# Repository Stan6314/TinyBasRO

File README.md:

Microcomputer TinyBasRO
======================

The TinyBasRO microcomputer is a very simple device that even an electrical engineering beginner should be able to assemble and put into operation. It resembles simple 8-bit computers from the 1980s. After assembly, it can be programmed very easily using the Tiny BASIC language, which should be manageable even for those who have never programmed before. The basis is a small 32-bit RISC-V processor cooperating with serial I2C memory, where the user-created program is stored.

A microcomputer is suitable for the first introduction to computing technology when teaching hardware and software. It can be used not only for educational purposes, but can also be used as a control element for simple electronic devices.

Technical data for TinyBasRO
----------------------------

*   TinyBasHW_KiCad - HW documents (schematic and printed circuit board) in KiCad 9.0 format
*   src - Source files for TinyBasRO for CH32V003 created in ch32fun development environment
*   Bin - Compiled binary content in HEX format for direct loading into CH32V003 memory
*   Manuals - Manuals for HW, Tiny BASIC programming language and its examples and advice for beginners
*   EEPROM_examples - Contents of serial EEPROM memory in HEX format with examples of 8 ready-made Tiny BASIC sample programs for loading into microcomputer memory

Requirements for building and operating a TinyBasRO
---------------------------------------------------

*   Printed circuit board
*   Electrical components according to the list in the TinyBasRO_HW manual
*   WCHLinkE programmer for programming CH32V003
*   OLED display 128x128 with SH1107 driver
*   Keyboard CardKB from M5STACK
*   5V power supply

Using a microcomputer
---------------------

The assembled microcomputer only requires a 5 V power supply, OLED display 128x128 with SH1107 driver and CardKB keyboard. The board has several interfaces for connecting expansion modules via the I2C bus or controlled elements via the input/output connector. In addition, the TinyBasRO allows you to easily light up a string of up to 100 WS2812 LEDs compared to computer TinyBasRV.

After debugging the program, the TinyBasRO microcomputer can work independently without a monitor and keyboard and control, for example, some LED lighting effects.

* * *

Mikropočítač TinyBasRO
======================

Mikropočítač TinyBasRO je velmi jednoduché zařízení, které by měl dokázat sestavit a uvést do provozu i elektrotechnický začátečník. Podobá se jednoduchým 8bitovým počítačům z 80tých let. Po sestavení jej lze velmi jednoduše programovat pomocí jazyka Tiny BASIC, který by měl zvládnout i ten, kdo dříve neprogramoval. Základem je malý 32bitový RISC-V procesor spolupracující se sériovou I2C pamětí, kam se ukládá uživatelem tvořený program.

Mikropočítač je vhodný pro první seznámení s výpočetní technikou při výuce technického i programového vybavení. Může být použit nejen pro výukové účely, ale lze jej nasadit jako řídicí prvek pro jednoduché elektronické přístroje.

Technické podklady pro TinyBasRO
--------------------------------

*   TinyBasHW_KiCad - HW podklady (schéma a plošný spoj) ve formátu programu KiCad 9.0
*   src - Zdrojové soubory k TinyBasRO pro CH32V003 vytvořené v prostředí ch32fun
*   Bin - Přeložený binární obsah ve formátu HEX pro přímé nahrání do paměti CH32V003
*   Manuals - Manuály pro HW, programovací jazyk Tiny BASIC a jeho příklady a rady pro začátečníky
*   EEPROM_examples - Obsah sériové EEPROM paměti ve formátu HEX s příklady 8 hotových ukázkových programů Tiny BASIC pro nahrání do paměti mikropočítače

Požadavky pro stavbu a provoz TinyBasRO
---------------------------------------

*   Deska plošného spoje
*   Elektrotechnické součástky podle seznamu v manuálu TinyBasRO_HW
*   Programátor WCHLinkE pro naprogramování CH32V003
*   OLED displej 128x128 s řadičem SH1107
*   Klávesnice CardKB od M5STACK
*   Napájecí zdroj 5 V

Použití mikropočítače
---------------------

Sestavený mikropočítač vyžaduje pouze napájecí zdroj 5 V, OLED displej 128x128 s řadičem SH1107 a klávesnici CardKB. Na desce je několik rozhraní pro připojení rozšiřujících modulů přes I2C sběrnici nebo ovládaných členů přes konektor vstupů/výstupů. Navíc proti počítači TinyBasRV umožňuje snadno rozsvěcovat řetězec až se 100 LED WS2812. 

Po odladění programu, může mikropočítač TinyBasRO pracovat samostatně bez monitoru a klávesnice a řídit např. nějaké světelné LED efekty.

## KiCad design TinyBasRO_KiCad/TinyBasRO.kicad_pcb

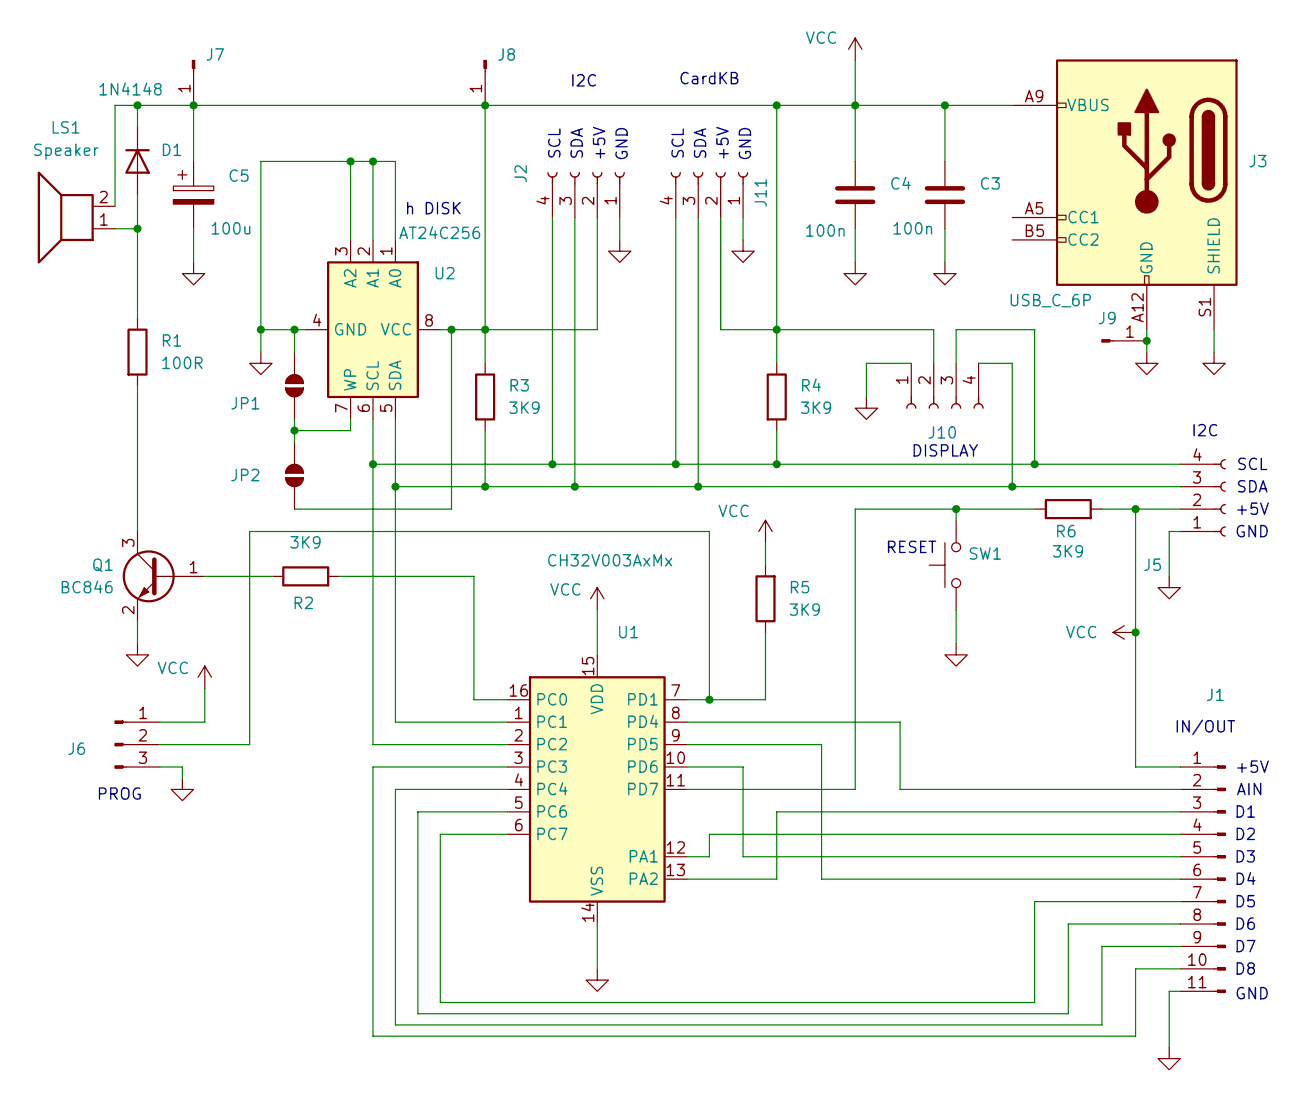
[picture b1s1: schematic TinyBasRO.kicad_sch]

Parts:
C3, C4: 100n; C_0805_2012Metric_Pad1.18x1.45mm_HandSolder
C5: 100u; CP_Radial_D7.5mm_P2.50mm
D1: 1N4148; D_MiniMELF_Handsoldering
J1: Conn_01x11_Pin; PinHeader_1x11_P2.54mm_Vertical
J2, J5: Conn_01x04_Socket; PinSocket_1x04_P2.54mm_Horizontal
J3: USB_C_6P; USB_C_Receptacle_GCT_USB4125-xx-x_6P_TopMnt_Horizontal
J6: Conn_01x03_Pin; PinHeader_1x03_P2.54mm_Vertical
J7, J8, J9: Conn_01x01_Pin; PinHeader_1x01_P2.54mm_Vertical
J10: Conn_01x04_Socket; PinSocket_1x04_P2.54mm_Vertical
J11: Conn_01x04_Socket; PinSocket_1x04_P2.00mm_Vertical
JP1, JP2: SolderJumper_2_Open; SolderJumper-2_P1.3mm_Open_RoundedPad1.0x1.5mm
LS1: Speaker; Indicator_PUI_AI-1440-TWT-24V-2-R
Q1: BC846; SOT-23
R1: 100R; R_0805_2012Metric_Pad1.20x1.40mm_HandSolder
R2, R3, R4, R5, R6: 3K9; R_0805_2012Metric_Pad1.20x1.40mm_HandSolder
SW1: SW_Push; SW_Tactile_SKHH_Angled
U1: CH32V003AxMx; SOP-16_3.9x9.9mm_P1.27mm
U2: AT24C256; SOIC-8_3.9x4.9mm_P1.27mm

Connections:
GND: C3.2, C4.2, C5.2, J1.11, J2.1, J3.A12 (GND), J3.B12 (GND), J3.S1 (SHIELD), J5.1, J6.3, J9.1, J10.1, J11.1, JP1.2 (B), Q1.2 (E), SW1.1, U1.14 (VSS), U2.1 (A0), U2.2 (A1), U2.3 (A2), U2.4 (GND)
unnamed: D1.2 (A), LS1.1, R1.1
unnamed: J1.2, U1.8 (PD4)
unnamed: J1.3, U1.13 (PA2)
unnamed: J1.4, U1.12 (PA1)
unnamed: J1.5, U1.10 (PD6)
unnamed: J1.6, U1.9 (PD5)
unnamed: J1.7, U1.6 (PC7)
unnamed: J1.8, U1.5 (PC6)
unnamed: J1.9, U1.4 (PC4)
unnamed: J1.10, U1.3 (PC3)
unnamed: J6.2, R5.1, U1.7 (PD1)
unnamed: J2.4, J5.4, J10.3, J11.4, R4.2, U1.2 (PC2), U2.6 (SCL)
unnamed: J2.3, J5.3, J10.4, J11.3, R3.2, U1.1 (PC1), U2.5 (SDA)
unnamed: JP1.1 (A), JP2.2 (B), U2.7 (WP)
unnamed: Q1.1 (B), R2.1
unnamed: Q1.3 (C), R1.2
unnamed: R2.2, U1.16 (PC0)
unnamed: R6.1, SW1.2, U1.11 (PD7)
VCC: C3.1, C4.1, C5.1, D1.1 (K), J1.1, J2.2, J3.A9 (VBUS), J3.B9 (VBUS), J5.2, J6.1, J7.1, J8.1, J10.2, J11.2, JP2.1 (A), LS1.2, R3.1, R4.1, R5.2, R6.2, U1.15 (VDD), U2.8 (VCC)

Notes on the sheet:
GND
+5V
AIN
SDA
DISPLAY
IN/OUT
I2C
SCL
RESET
h DISK
CardKB
PROG

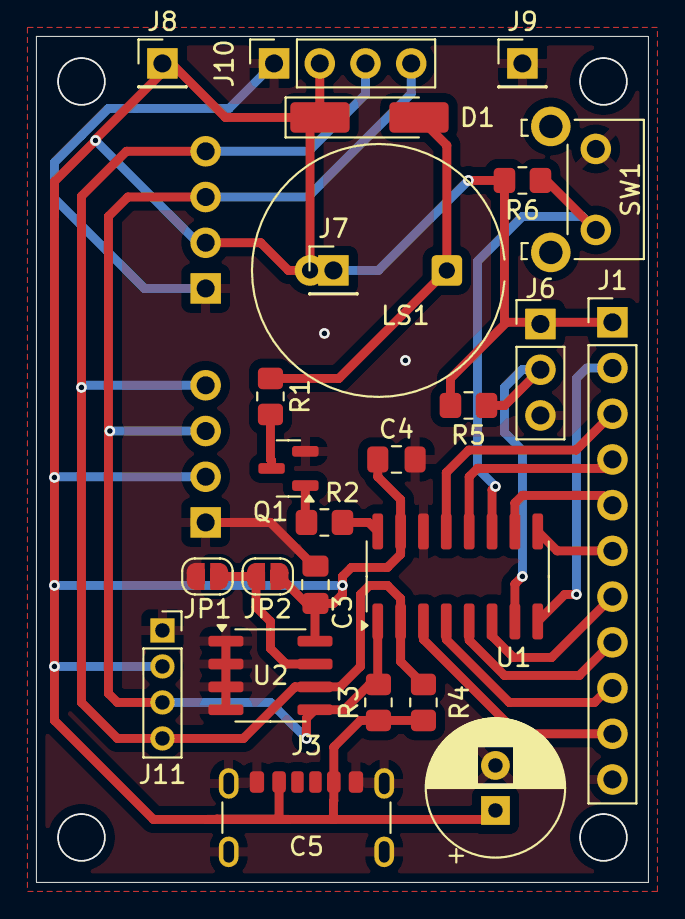
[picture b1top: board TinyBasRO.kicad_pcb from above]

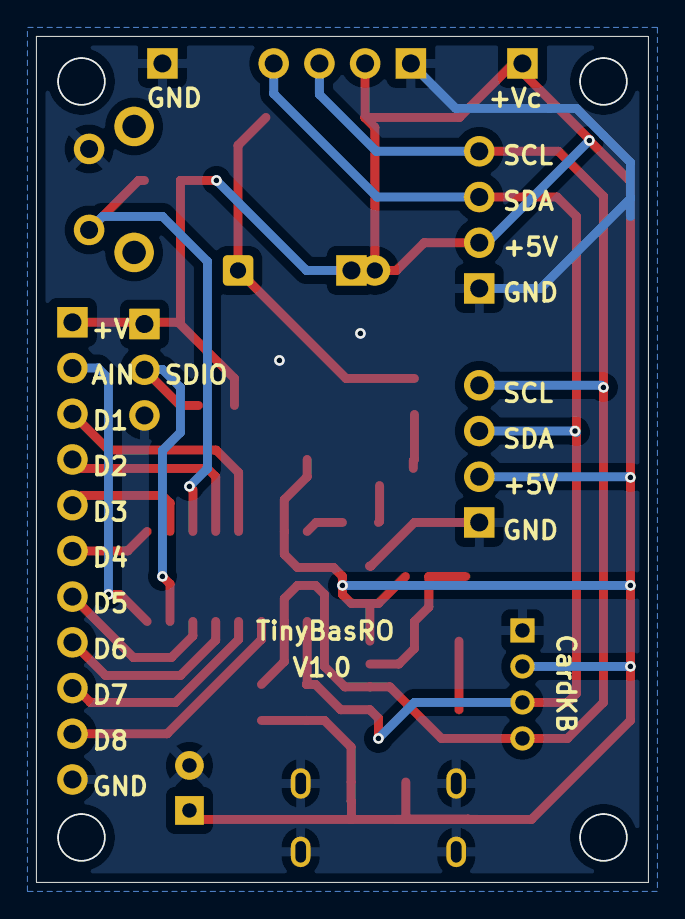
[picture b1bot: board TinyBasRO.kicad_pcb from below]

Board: 2 copper layers, 34.0 x 47.0 mm, 27 parts (2 on the bottom side), 20 nets.

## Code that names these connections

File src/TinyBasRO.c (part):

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    RCC->APB1PCENR |= RCC_APB1Periph_I2C1; 
	RCC->APB2PCENR |= RCC_APB2Periph_GPIOC | RCC_APB2Periph_AFIO;
    // Reset I2C1 to init all regs
	// PC1 is SDA, 30MHz Output, alt func, open-drain
	GPIOC->CFGLR &= ~(0xf<<(4*1));
	GPIOC->CFGLR |= (GPIO_Speed_10MHz | GPIO_CNF_OUT_OD_AF)<<(4*1);
	// PC2 is SCL, 30MHz Output, alt func, open-drain
	GPIOC->CFGLR &= ~(0xf<<(4*2));
	GPIOC->CFGLR |= (GPIO_Speed_10MHz | GPIO_CNF_OUT_OD_AF)<<(4*2);
    // set freq
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	RCC->CFGR0 &= ~(0x1F<<11);
	// Enable GPIOD and ADC
	RCC->APB2PCENR |= RCC_APB2Periph_ADC1;
	// PD4 is analog input chl 7
	GPIOD->CFGLR &= ~(0xf<<(4*4));	// CNF = 00: Analog, MODE = 00: Input
	// Reset the ADC to init all regs
	RCC->APB2PRSTR |= RCC_APB2Periph_ADC1;
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              switch(*numPin & 0x07)
              { // Cursor will be moved only in 4 cases - "p" is only flag
                case 0: {      // Is input 8?
                    funPinMode( PC3, GPIO_CFGLR_IN_PUPD ); funDigitalWrite( PC3, 1 );
                    *numOnLine = funDigitalRead( PC3 );
                    }  break; 
                case 1: {      // Is input 1?
                    funPinMode( PA2, GPIO_CFGLR_IN_PUPD ); funDigitalWrite( PA2, 1 );
                    *numOnLine = funDigitalRead( PA2 );
                    }  break; 
                case 2: {      // Is input 2?
                    funPinMode( PA1, GPIO_CFGLR_IN_PUPD ); funDigitalWrite( PA1, 1 );
                    *numOnLine = funDigitalRead( PA1 );
                    }  break; 
                case 3: {      // Is input 3?
                    funPinMode( PD6, GPIO_CFGLR_IN_PUPD ); funDigitalWrite( PD6, 1 );
                    *numOnLine = funDigitalRead( PD6 );
                    }  break; 
                case 4: {      // Is input 4?
                    funPinMode( PD5, GPIO_CFGLR_IN_PUPD ); funDigitalWrite( PD5, 1 );
                    *numOnLine = funDigitalRead( PD5 );
                    }  break; 
                case 5: {      // Is input 5?
                    funPinMode( PC7, GPIO_CFGLR_IN_PUPD ); funDigitalWrite( PC7, 1 );
                    *numOnLine = funDigitalRead( PC7 );
                    }  break; 
                case 6: {      // Is input 6?
                    funPinMode( PC6, GPIO_CFGLR_IN_PUPD ); funDigitalWrite( PC6, 1 );
                    *numOnLine = funDigitalRead( PC6 );
                    }  break; 
                case 7: {      // Is input 7?
                    funPinMode( PC4, GPIO_CFGLR_IN_PUPD ); funDigitalWrite( PC4, 1 );
                    *numOnLine = funDigitalRead( PC4 );
                    }  break; 
                }
            } else WriteErrMsg("Error Input!");
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        RemoveNextWhtSP();
        if((numOnLine = isExpression()) != NULL)
        {
            funPinMode( PA2, GPIO_CFGLR_OUT_10Mhz_PP ); // Set as output
            GPIOA->BSHR = 0x00040000;           // and clear it
            int LEDcount = *numOnLine;           // Get how many LEDs is connected
            if(LEDcount > 99) LEDcount = 100;   // Maximum lenght of array
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              switch(*numOnLine & 0x07)
              { // Set output pin
                case 0: {      // Is output 8?
                    funPinMode( PC3, GPIO_CFGLR_OUT_10Mhz_PP ); 
                    if(outValue) {funDigitalWrite( PC3, FUN_HIGH );} else {funDigitalWrite( PC3, FUN_LOW );}
                    }  break; 
                case 1: {      // Is output 1?
                    funPinMode( PA2, GPIO_CFGLR_OUT_10Mhz_PP ); 
                    if(outValue) {funDigitalWrite( PA2, FUN_HIGH );} else {funDigitalWrite( PA2, FUN_LOW );}
                    }  break; 
                case 2: {      // Is output 2?
                    funPinMode( PA1, GPIO_CFGLR_OUT_10Mhz_PP ); 
                    if(outValue) {funDigitalWrite( PA1, FUN_HIGH );} else {funDigitalWrite( PA1, FUN_LOW );}
                    }  break; 
                case 3: {      // Is output 3?
                    funPinMode( PD6, GPIO_CFGLR_OUT_10Mhz_PP ); 
                    if(outValue) {funDigitalWrite( PD6, FUN_HIGH );} else {funDigitalWrite( PD6, FUN_LOW );}
                    }  break; 
                case 4: {      // Is output 4?
                    funPinMode( PD5, GPIO_CFGLR_OUT_10Mhz_PP ); 
                    if(outValue) {funDigitalWrite( PD5, FUN_HIGH );} else {funDigitalWrite( PD5, FUN_LOW );}
                    }  break; 
                case 5: {      // Is output 5?
                    funPinMode( PC7, GPIO_CFGLR_OUT_10Mhz_PP ); 
                    if(outValue) {funDigitalWrite( PC7, FUN_HIGH );} else {funDigitalWrite( PC7, FUN_LOW );}
                    }  break; 
                case 6: {      // Is output 6?
                    funPinMode( PC6, GPIO_CFGLR_OUT_10Mhz_PP ); 
                    if(outValue) {funDigitalWrite( PC6, FUN_HIGH );} else {funDigitalWrite( PC6, FUN_LOW );}
                    }  break; 
                case 7: {      // Is output 7?
                    funPinMode( PC4, GPIO_CFGLR_OUT_10Mhz_PP ); 
                    if(outValue) {funDigitalWrite( PC4, FUN_HIGH );} else {funDigitalWrite( PC4, FUN_LOW );}
                    }  break; 
                }
            } else WriteErrMsg("Error output pin!");
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
	funGpioInitAll();  // Enable GPIOs
    // Prepare speaker output
    funPinMode( PC0, GPIO_CFGLR_OUT_10Mhz_PP ); 
    funDigitalWrite( PC0, FUN_LOW );
    IIC_Init();     // Initialize I2C module
    // Initialize SysTick to trigger an IRQ with auto-reload, using HCLK/1 as clock source
	// Reset any pre-existing configuration
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
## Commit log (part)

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2025-12-24 Initial release
2025-12-29 Added program examples
2025-12-29 Source code added
2026-01-02 Examples added
2026-01-28 Moved HEX to ZIP file
